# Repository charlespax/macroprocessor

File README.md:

# macroprocessor
A project to create a microprocessor optimized for human visual verification

# Introduction
A user should be able to trust the output of a computational device without having to trust
the computatoinal device itself.

# Application
## Cryptographic security
Bitcoin

# Design
The design is not optimized for price, area, power, efficiency, yield, or other 
traditional parameter. The design is optimized for human readability and understanding.

## Requirements
- MUST be visible to a human with minimal optical magnification
- An integrated circuit design layout SHOULD aid understanding
- IC layout SHOULD correspond to the layout as seen in a digitial simulation
- Microprocessor design architecture SHOULD be optimized for understanding
- The registers or other circuitry MAY emit light
- MAY have features to aid cryptography
- MAY have serial output for debugging or other purposes

## Design notes
The overall chip layout and data flow SHOULD run from left to right.

Logical elements SHOULD have inputs on the left and outputs on the right

The metal layer or other features MUST NOT obscure any features such that 
the circuit can not be verified visually.

Chip packaging MUST NOT obscure the electrical path from the IC to the
package pins.

The design MAY use multiple IC components if each component meets the
requirements of this document.

The design MAY include wire-bonded components

# Notes
- RISC-V RV32I or RV32E are candidates
- Research making a Forth-native processor
- Can the macroprocessor be made using the same process as LEDs?
- Can a wafer be put through a secondary LED process to create registers that
  emit light?
- What is the current state of light-emitting transistors (LETs)?
- Can I use diode logic and use LEDs?
- I believe the normal silicon process cannot be used to create features that
  emit light because the band gap of silicon is too greaet. True?
- RISC-V would be a great choice if it can be visually verified. This has the 
  advantage that many more eyes would be on the chip. However, I think it is
  more important to make choices that result in more users in verifying their
  own devices.
- Check out https://zeroToASICCourse.com - this is a course for designing and ordering
  your own chip designs.
- Check out https://developers.google.com/silicon - Google's wafer batching
  program for open source designs. Cool, but I am happy to pay if reasonable.
- MAY take an external diode-based ROM
- Is there anything about this processor that would make it bad at cryptographic
  functions? Minimal circuitry could be included to address issues.
- Can x-ray crystalography be used to verify the surface of an IC?
- https://www.skywatertechnology.com is a US-based silicon fab. 
- What happens to the equipment from old semiconductor fabrication technologies?
- Fab technologies: https://en.wikipedia.org/wiki/Semiconductor\_device\_fabrication
- Are there fabs that use old technologies for new chips?
- Wire bonding can be used in places where the metal layer would obscure layers below
- wire bonding can be used as jumpers that can be cut to permanently disable a ffeature
- Rather than wire bonding, the connections can be routed to the outside of the package,
  so they can be explicetly enabled
- Maybe multi gate transistors can be used on such large features if one large gate is
  not appropriate
- Make the binary instruction decoding physicallyl easy to see on the die. Put them
  in the same order you would find them in a specification table
- Is silicon transparent to any frequency of light? If so, maybe  this can be
  used for verification and would be a design consideration.

# Conventions
The keywords below are to be interpreted as described in BCP14 [RFC2119] [RFC8174].
- MUST
- MUST NOT
- REQUIRED
- SHOULD
- SHOULD NOT
- RECOMMENDED
- NOT RECOMMENDED
- MAY
- OPTIONAL

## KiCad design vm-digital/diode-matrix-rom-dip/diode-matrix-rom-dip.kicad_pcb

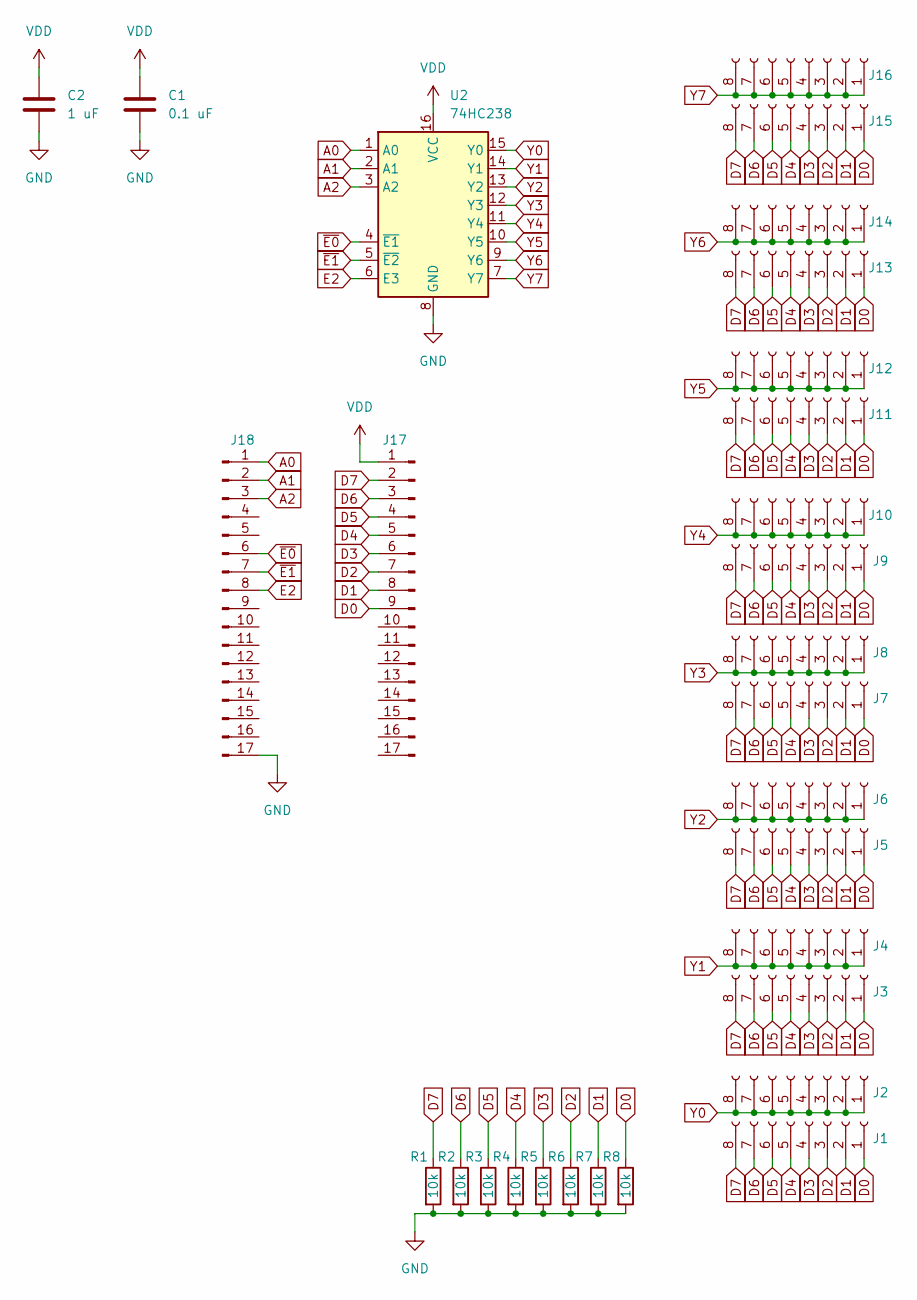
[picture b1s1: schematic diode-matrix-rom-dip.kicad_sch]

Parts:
C1: 0.1 uF; C_1206_3216Metric_Pad1.33x1.80mm_HandSolder
C2: 1 uF; C_1206_3216Metric_Pad1.33x1.80mm_HandSolder
J1, J2, J3, J4, J5, J6, J7, J8, J9, J10, J11, J12, J13, J14, J15, J16: Conn_01x08_Socket; PinSocket_1x08_P2.54mm_Vertical
J17, J18: Conn_01x17_Pin; PinHeader_1x17_P2.54mm_Vertical
R1, R2, R3, R4, R5, R6, R7, R8: 10k; R_0201_0603Metric
U2: 74HC238; DIP-16_W7.62mm

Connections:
A0: J18.1, U2.1 (A0)
A1: J18.2, U2.2 (A1)
A2: J18.3, U2.3 (A2)
D0: J1.1, J3.1, J5.1, J7.1, J9.1, J11.1, J13.1, J15.1, J17.9, R8.1
D1: J1.2, J3.2, J5.2, J7.2, J9.2, J11.2, J13.2, J15.2, J17.8, R7.1
D2: J1.3, J3.3, J5.3, J7.3, J9.3, J11.3, J13.3, J15.3, J17.7, R6.1
D3: J1.4, J3.4, J5.4, J7.4, J9.4, J11.4, J13.4, J15.4, J17.6, R5.1
D4: J1.5, J3.5, J5.5, J7.5, J9.5, J11.5, J13.5, J15.5, J17.5, R4.1
D5: J1.6, J3.6, J5.6, J7.6, J9.6, J11.6, J13.6, J15.6, J17.4, R3.1
D6: J1.7, J3.7, J5.7, J7.7, J9.7, J11.7, J13.7, J15.7, J17.3, R2.1
D7: J1.8, J3.8, J5.8, J7.8, J9.8, J11.8, J13.8, J15.8, J17.2, R1.1
E2: J18.8, U2.6 (E3)
GND: C1.2, C2.2, J18.17, R1.2, R2.2, R3.2, R4.2, R5.2, R6.2, R7.2, R8.2, U2.8 (GND)
VDD: C1.1, C2.1, J17.1, U2.16 (VCC)
Y0: J2.1, J2.2, J2.3, J2.4, J2.5, J2.6, J2.7, J2.8, U2.15 (Y0)
Y1: J4.1, J4.2, J4.3, J4.4, J4.5, J4.6, J4.7, J4.8, U2.14 (Y1)
Y2: J6.1, J6.2, J6.3, J6.4, J6.5, J6.6, J6.7, J6.8, U2.13 (Y2)
Y3: J8.1, J8.2, J8.3, J8.4, J8.5, J8.6, J8.7, J8.8, U2.12 (Y3)
Y4: J10.1, J10.2, J10.3, J10.4, J10.5, J10.6, J10.7, J10.8, U2.11 (Y4)
Y5: J12.1, J12.2, J12.3, J12.4, J12.5, J12.6, J12.7, J12.8, U2.10 (Y5)
Y6: J14.1, J14.2, J14.3, J14.4, J14.5, J14.6, J14.7, J14.8, U2.9 (Y6)
Y7: J16.1, J16.2, J16.3, J16.4, J16.5, J16.6, J16.7, J16.8, U2.7 (Y7)
~E0: J18.6, U2.4 (~E1)
~E1: J18.7, U2.5 (~E2)

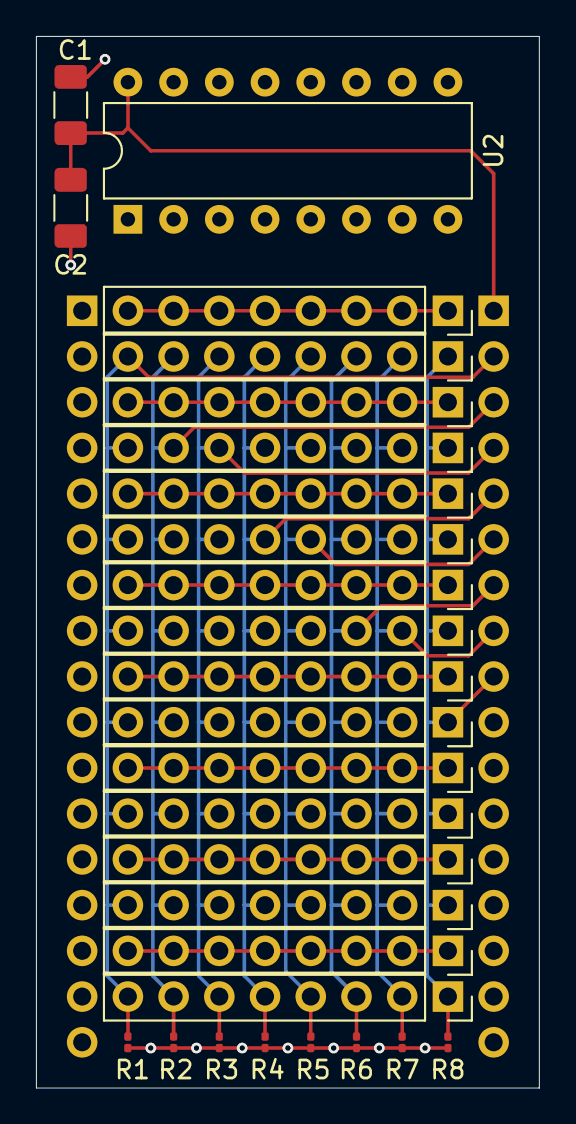
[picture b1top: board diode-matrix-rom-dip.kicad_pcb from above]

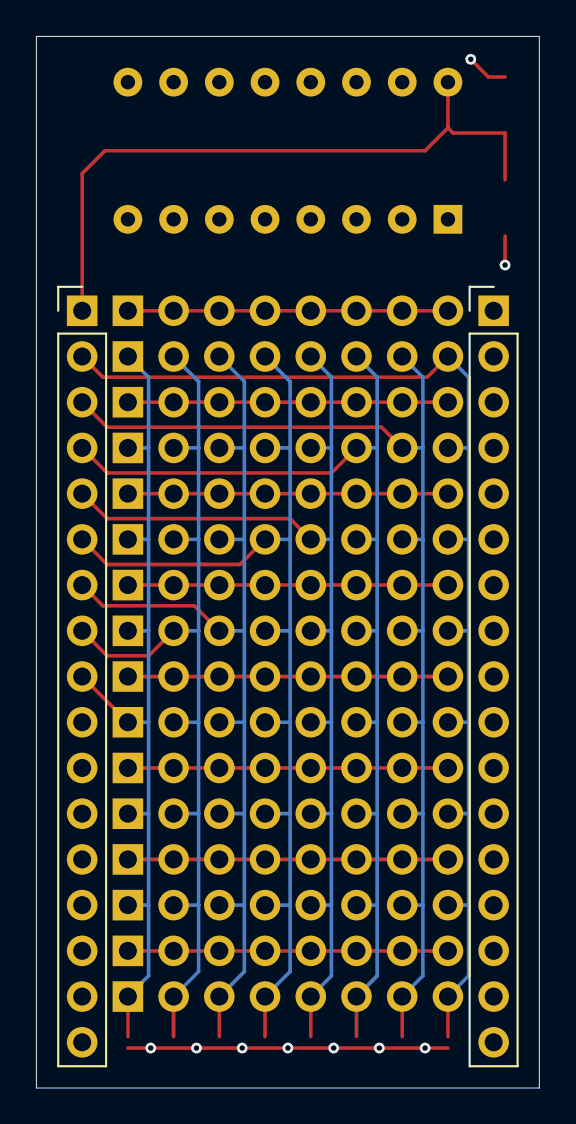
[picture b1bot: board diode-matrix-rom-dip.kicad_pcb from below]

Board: 4 copper layers, 27.9 x 58.4 mm, 29 parts (2 on the bottom side), 24 nets.

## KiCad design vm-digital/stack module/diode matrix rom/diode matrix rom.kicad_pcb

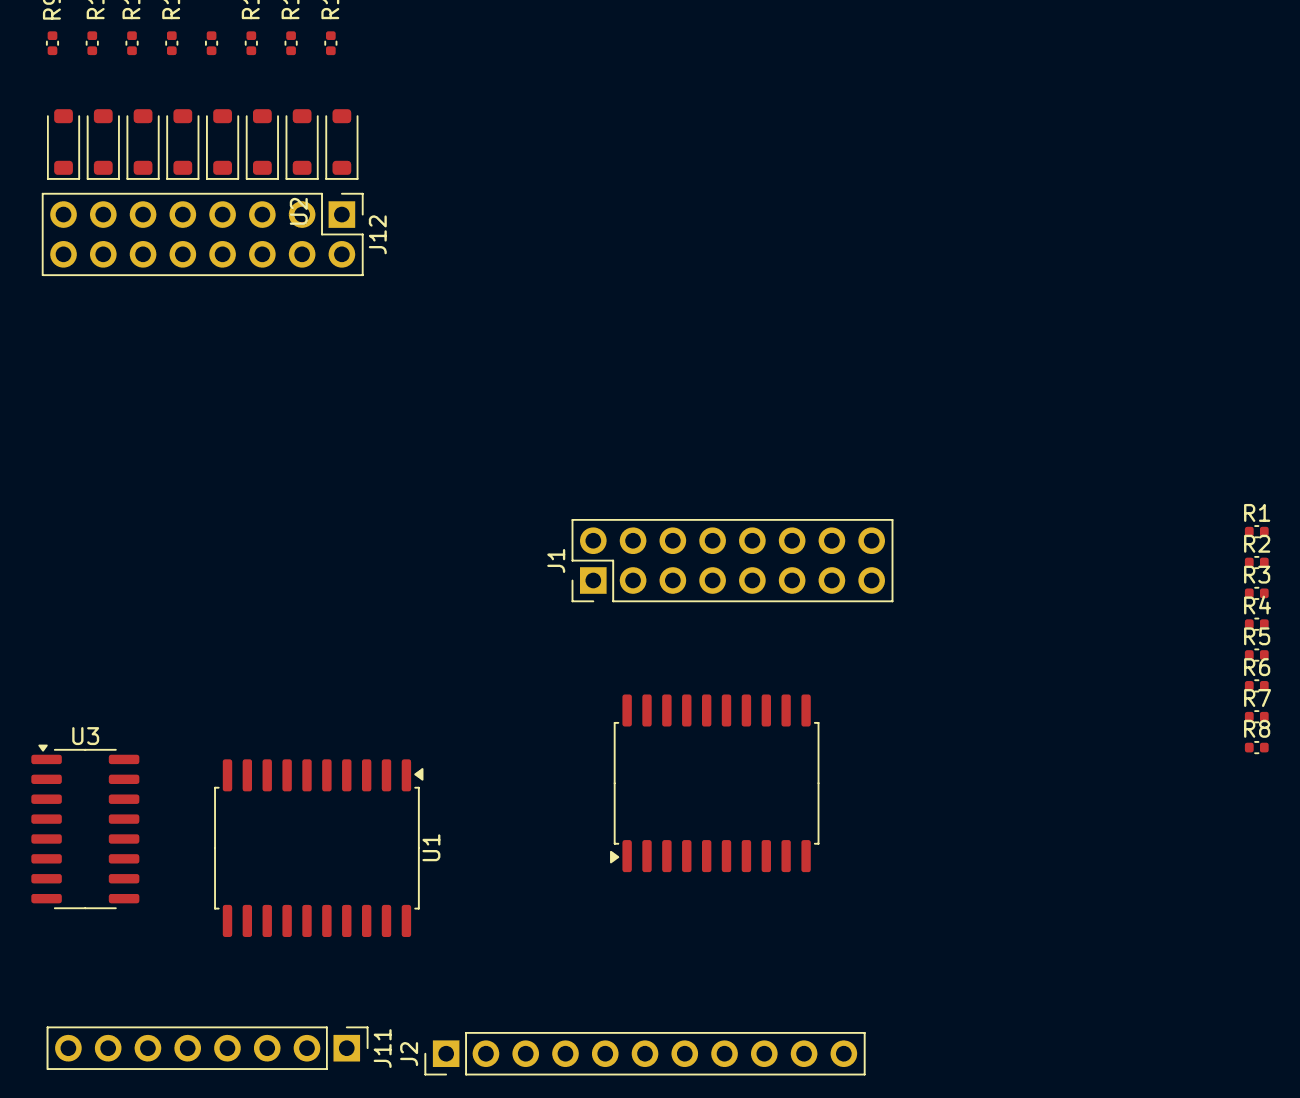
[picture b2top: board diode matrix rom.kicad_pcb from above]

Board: 2 copper layers, 31 parts (0 on the bottom side), 47 nets, no tracks yet.

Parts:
D1, D2, D3, D4, D5, D6, D7, D8: D; D_SOD-123
J1, J12: DIN41612_02x16_AB; PinHeader_2x08_P2.54mm_Vertical
J2: Conn_01x11_Pin; PinHeader_1x11_P2.54mm_Vertical
J11: Conn_01x08_Pin; PinHeader_1x08_P2.54mm_Vertical
R1, R2, R3, R4, R5, R6, R7, R8, R9, R10, R11, R12, R13, R14, R15, R16: 10k; C_0402_1005Metric
U1: 74LS540; SOIC-20W_7.5x12.8mm_P1.27mm
U2: 74HC688; SOIC-20W_7.5x12.8mm_P1.27mm
U3: 74HC238; SOIC-16_3.9x9.9mm_P1.27mm

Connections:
B0: D1.2 (A), R16.2, U1.2 (A0)
B1: D2.2 (A), R15.2, U1.3 (A1)
B2: D4.2 (A), R14.2, U1.4 (A2)
B3: D3.2 (A), R13.2, U1.5 (A3)
B4: D8.2 (A), R12.2, U1.6 (A4)
B5: D7.2 (A), R11.2, U1.7 (A5)
B6: D6.2 (A), R10.2, U1.8 (A6)
B7: D5.2 (A), R9.2, U1.9 (A7)
GND: R1.1, R2.1, R3.1, R4.1, R5.1, R6.1, R7.1, R8.1, U1.10 (GND), U2.10 (GND), U3.8 (GND)
unnamed: D1.1 (K), J12.1
unnamed: D2.1 (K), J12.3
unnamed: D3.1 (K), J12.7
unnamed: D4.1 (K), J12.5
unnamed: D5.1 (K), J12.15
unnamed: D6.1 (K), J12.13
unnamed: D7.1 (K), J12.11
unnamed: D8.1 (K), J12.9
unnamed: J1.2, R1.2, U2.2 (P0)
unnamed: J1.4, R2.2, U2.4 (P1)
unnamed: J1.6, R3.2, U2.6 (P2)
unnamed: J1.8, R4.2, U2.8 (P3)
unnamed: J1.10, R5.2, U2.11 (P4)
unnamed: J1.12, R6.2, U2.13 (P5)
unnamed: J1.14, R7.2, U2.15 (P6)
unnamed: J1.16, R8.2, U2.17 (P7)
unnamed: J2.1, U3.1 (A0)
unnamed: J2.2, U3.2 (A1)
unnamed: J2.3, U3.3 (A2)
unnamed: J2.4, U2.3 (R0)
unnamed: J2.5, U2.5 (R1)
unnamed: J2.6, U2.7 (R2)
unnamed: J2.7, U2.9 (R3)
unnamed: J2.8, U2.12 (R4)
unnamed: J2.9, U2.14 (R5)
unnamed: J2.10, U2.16 (R6)
unnamed: J2.11, U2.18 (R7)
unnamed: J11.1, U1.18 (Y0)
unnamed: J11.2, U1.17 (Y1)
unnamed: J11.3, U1.16 (Y2)
unnamed: J11.4, U1.15 (Y3)
unnamed: J11.5, U1.14 (Y4)
unnamed: J11.6, U1.13 (Y5)
unnamed: J11.7, U1.12 (Y6)
unnamed: J11.8, U1.11 (Y7)
unnamed: U1.1 (G1), U1.19 (G2), U2.19 (P=R), U3.4 (~E0), U3.5 (~E1)
VDD: J1.1, J1.3, J1.5, J1.7, J1.9, J1.11, J1.13, J1.15, R9.1, R10.1, R11.1, R12.1, R13.1, R14.1, R15.1, R16.1, U1.20 (VCC), U2.20 (VCC), U3.6 (E2), U3.16 (VCC)
W0: J12.2, J12.4, J12.6, J12.8, J12.10, J12.12, J12.14, J12.16, U3.15 (~Y0)

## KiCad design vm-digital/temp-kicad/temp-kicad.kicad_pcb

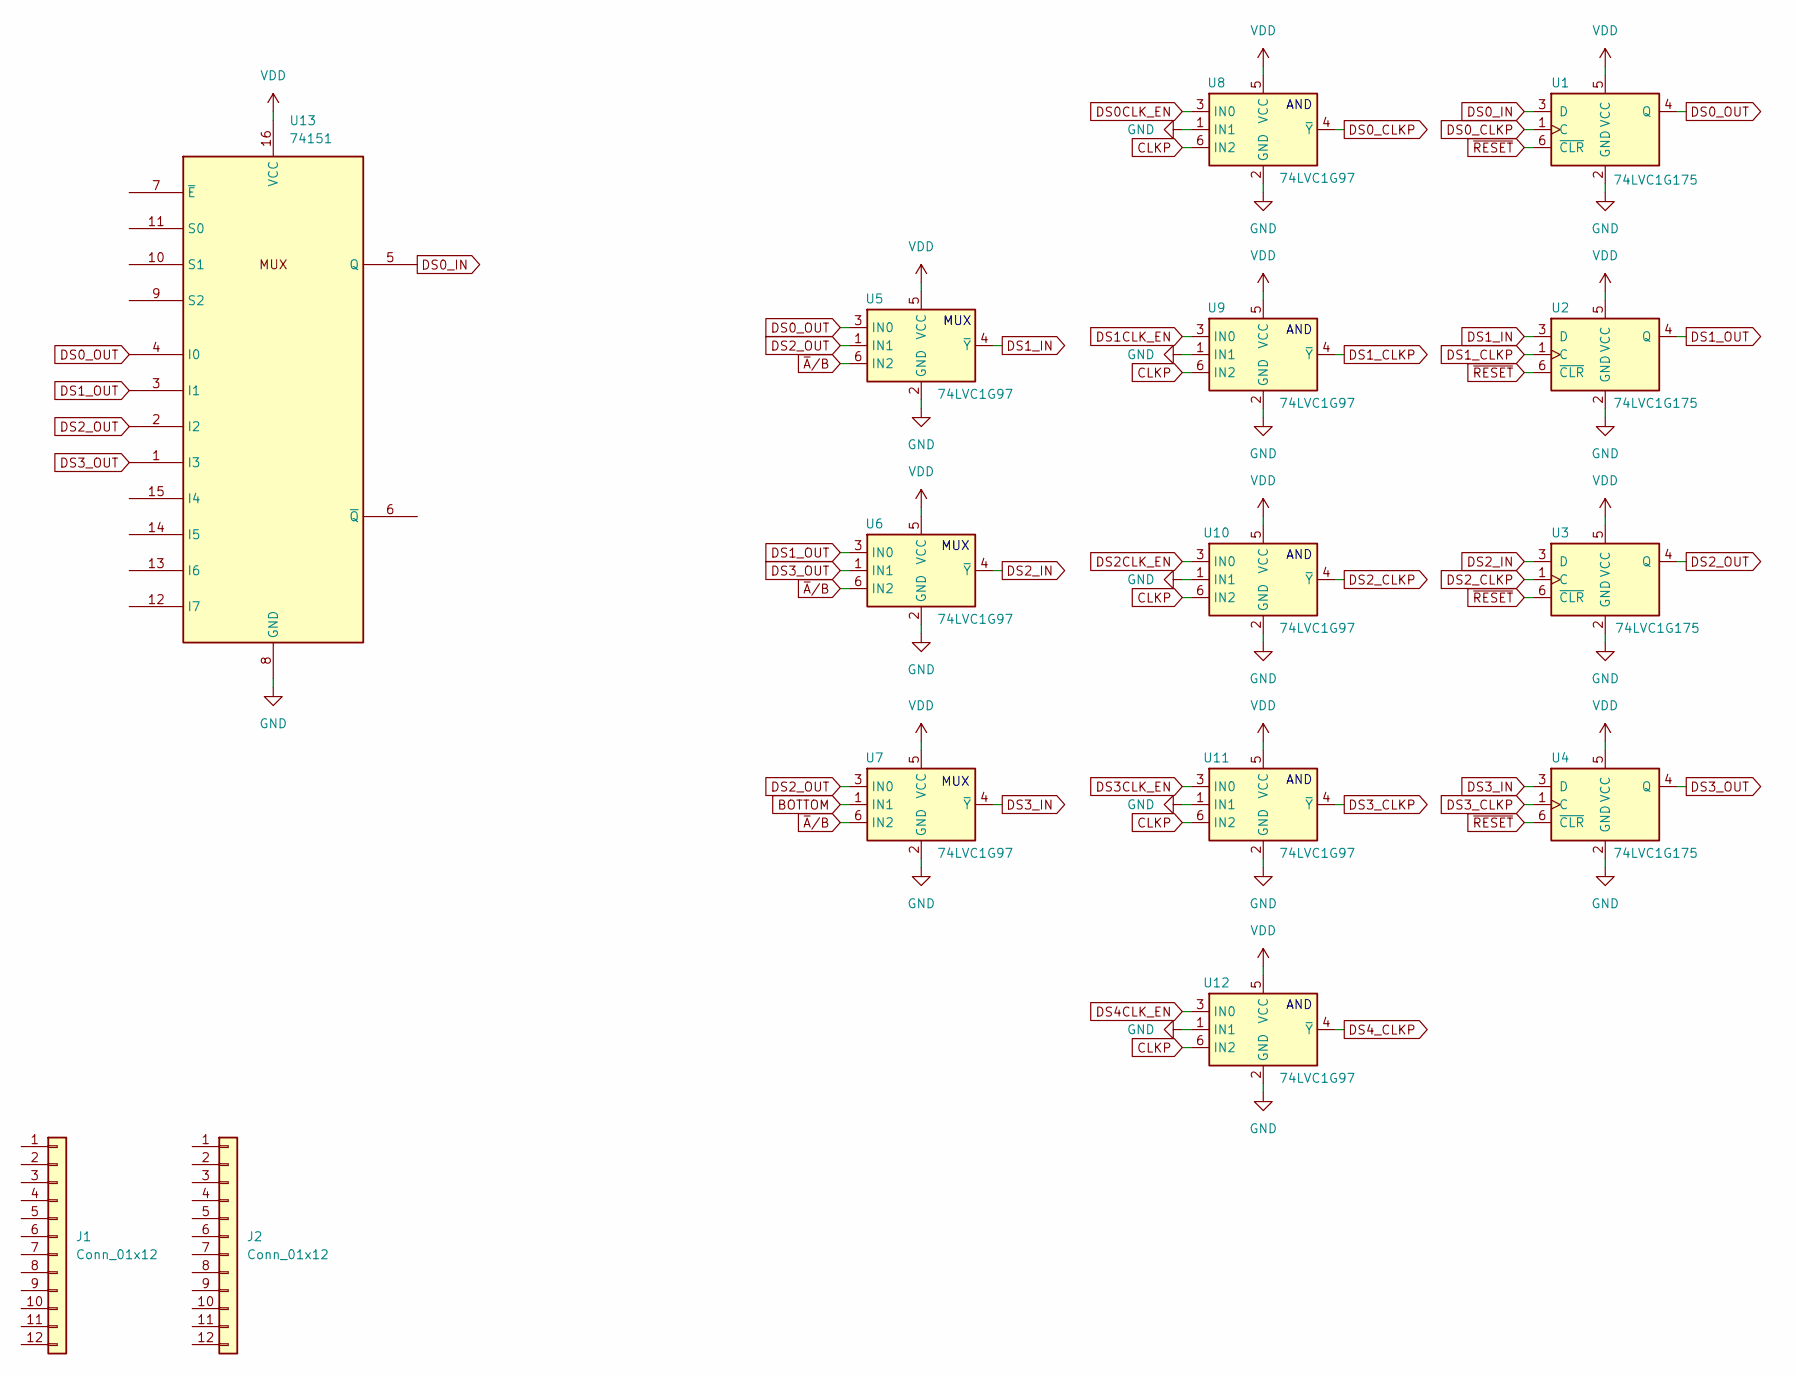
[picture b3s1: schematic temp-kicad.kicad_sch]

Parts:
J1, J2: Conn_01x12; PinHeader_1x12_P2.54mm_Vertical
U1, U2, U3, U4: 74LVC1G175; SOT-23-6_Handsoldering
U5, U6, U7, U8, U9, U10, U11, U12: 74LVC1G97; SOT-23-6_Handsoldering
U13: 74151; SOIC-16_3.9x9.9mm_P1.27mm

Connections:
BOTTOM: U7.1 (IN1)
CLKP: U8.6 (IN2), U9.6 (IN2), U10.6 (IN2), U11.6 (IN2), U12.6 (IN2)
DS0CLK_EN: U8.3 (IN0)
DS0_CLKP: U1.1 (C), U8.4 (~Y)
DS0_IN: U1.3 (D), U13.5 (Q)
DS0_OUT: U1.4 (Q), U5.3 (IN0), U13.4 (I0)
DS1CLK_EN: U9.3 (IN0)
DS1_CLKP: U2.1 (C), U9.4 (~Y)
DS1_IN: U2.3 (D), U5.4 (~Y)
DS1_OUT: U2.4 (Q), U6.3 (IN0), U13.3 (I1)
DS2CLK_EN: U10.3 (IN0)
DS2_CLKP: U3.1 (C), U10.4 (~Y)
DS2_IN: U3.3 (D), U6.4 (~Y)
DS2_OUT: U3.4 (Q), U5.1 (IN1), U7.3 (IN0), U13.2 (I2)
DS3CLK_EN: U11.3 (IN0)
DS3_CLKP: U4.1 (C), U11.4 (~Y)
DS3_IN: U4.3 (D), U7.4 (~Y)
DS3_OUT: U4.4 (Q), U6.1 (IN1), U13.1 (I3)
DS4CLK_EN: U12.3 (IN0)
DS4_CLKP: U12.4 (~Y)
GND: U1.2 (GND), U2.2 (GND), U3.2 (GND), U4.2 (GND), U5.2 (GND), U6.2 (GND), U7.2 (GND), U8.1 (IN1), U8.2 (GND), U9.1 (IN1), U9.2 (GND), U10.1 (IN1), U10.2 (GND), U11.1 (IN1), U11.2 (GND), U12.1 (IN1), U12.2 (GND), U13.8 (GND)
VDD: U1.5 (VCC), U2.5 (VCC), U3.5 (VCC), U4.5 (VCC), U5.5 (VCC), U6.5 (VCC), U7.5 (VCC), U8.5 (VCC), U9.5 (VCC), U10.5 (VCC), U11.5 (VCC), U12.5 (VCC), U13.16 (VCC)
~A/B: U5.6 (IN2), U6.6 (IN2), U7.6 (IN2)
~RESET: U1.6 (~CLR), U2.6 (~CLR), U3.6 (~CLR), U4.6 (~CLR)

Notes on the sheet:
MUX
AND

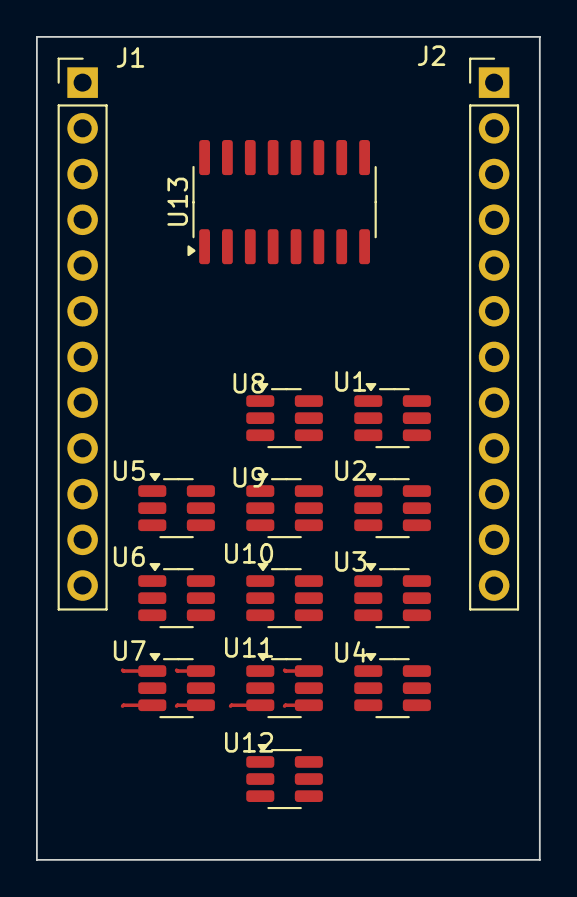
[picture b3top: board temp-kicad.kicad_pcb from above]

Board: 4 copper layers, 27.9 x 45.7 mm, 15 parts (0 on the bottom side), 17 nets.

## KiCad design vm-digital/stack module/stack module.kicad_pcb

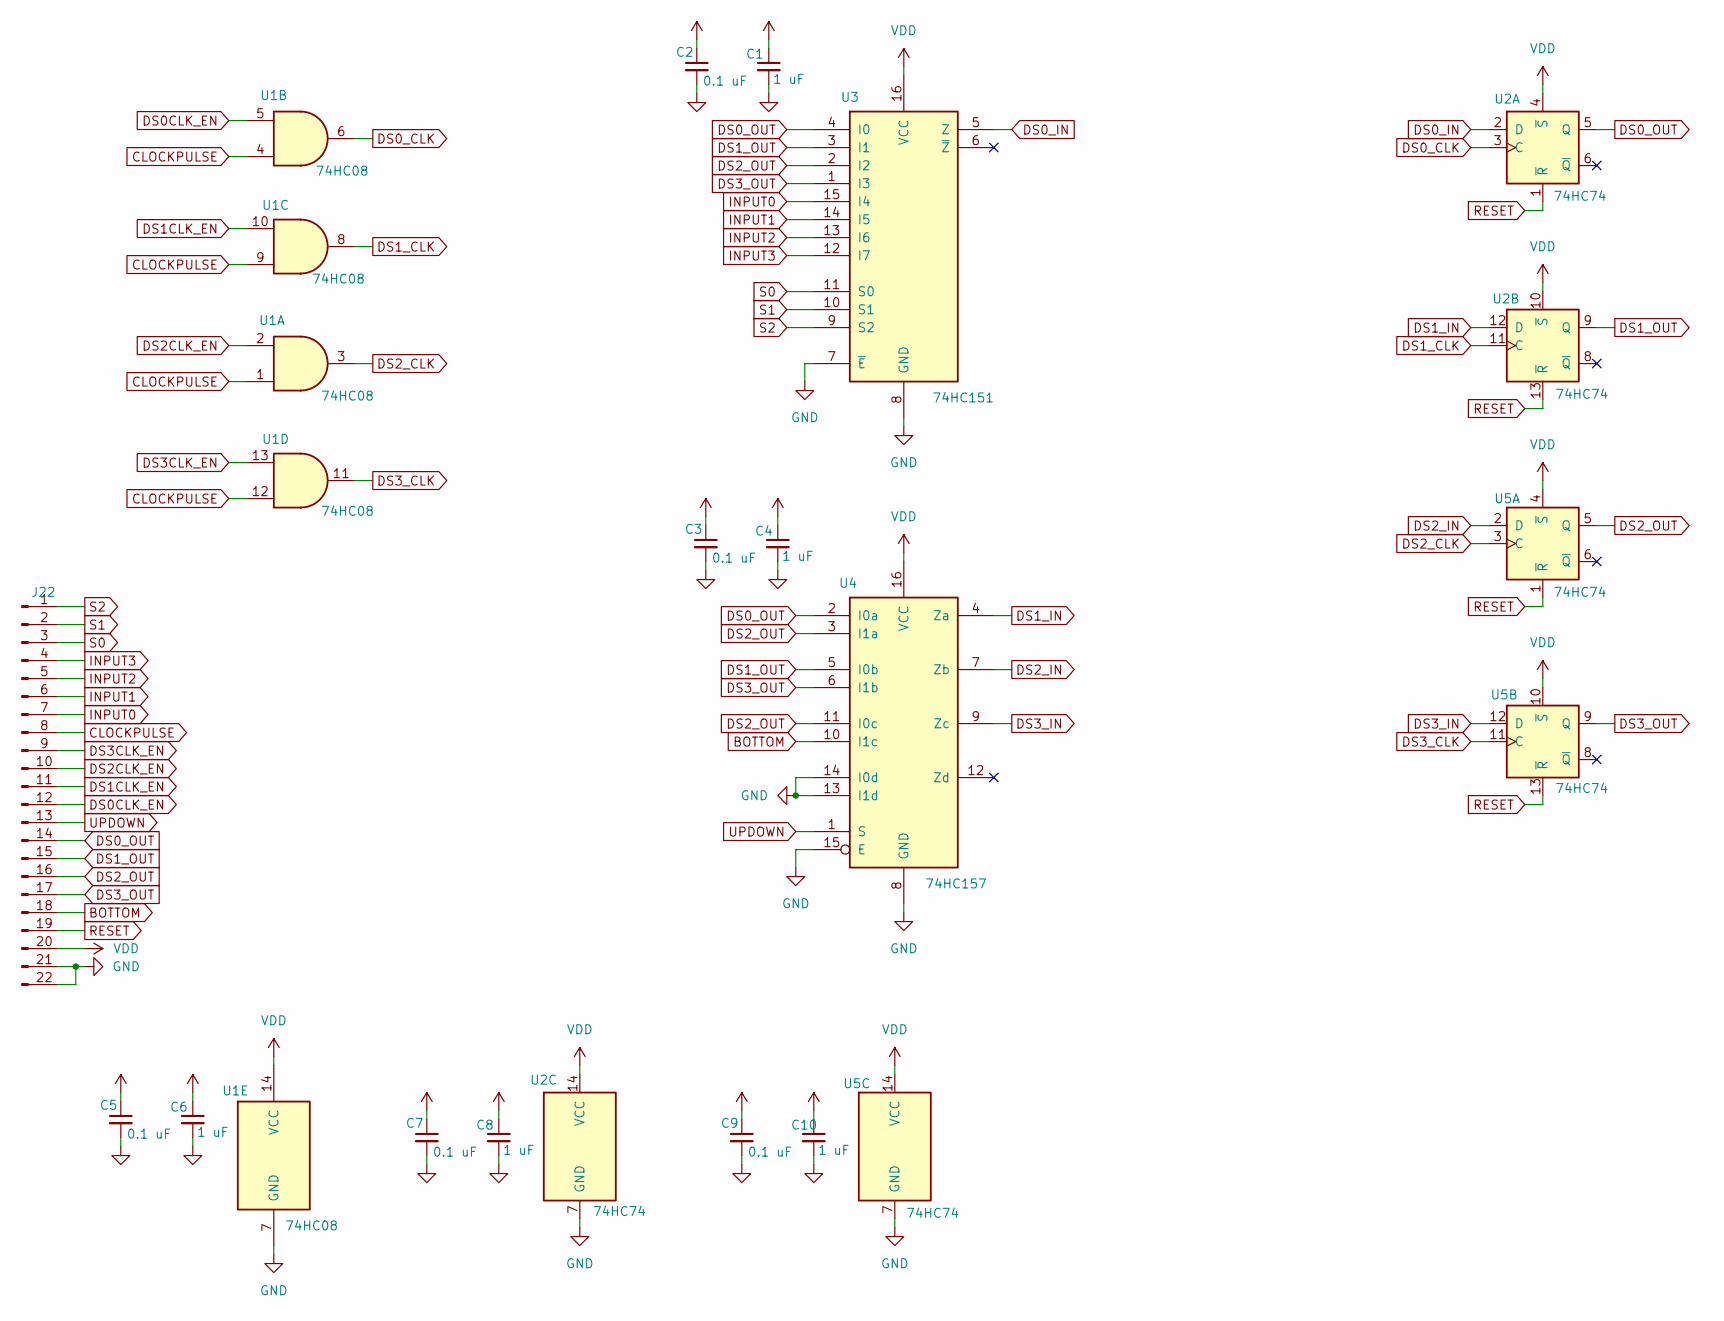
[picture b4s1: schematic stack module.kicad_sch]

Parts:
C1, C4, C6, C8, C10: 1 uF; C_1206_3216Metric_Pad1.33x1.80mm_HandSolder
C2, C3, C5, C7, C9: 0.1 uF; C_1206_3216Metric_Pad1.33x1.80mm_HandSolder
J22: Conn_01x22_Pin; PinHeader_1x22_P2.54mm_Vertical
U1: 74HC08; DIP-14_W7.62mm_Socket_LongPads
U2, U5: 74HC74; DIP-14_W7.62mm_Socket_LongPads
U3: 74HC151; DIP-16_W7.62mm_Socket_LongPads
U4: 74HC157; DIP-16_W7.62mm_Socket_LongPads

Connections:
BOTTOM: J22.18, U4.10 (I1c)
CLOCKPULSE: J22.8, U1.1, U1.4, U1.9, U1.12
DS0CLK_EN: J22.12, U1.5
DS0_CLK: U1.6, U2.3 (C)
DS0_IN: U2.2 (D), U3.5 (Z)
DS0_OUT: J22.14, U2.5 (Q), U3.4 (I0), U4.2 (I0a)
DS1CLK_EN: J22.11, U1.10
DS1_CLK: U1.8, U2.11 (C)
DS1_IN: U2.12 (D), U4.4 (Za)
DS1_OUT: J22.15, U2.9 (Q), U3.3 (I1), U4.5 (I0b)
DS2CLK_EN: J22.10, U1.2
DS2_CLK: U1.3, U5.3 (C)
DS2_IN: U4.7 (Zb), U5.2 (D)
DS2_OUT: J22.16, U3.2 (I2), U4.3 (I1a), U4.11 (I0c), U5.5 (Q)
DS3CLK_EN: J22.9, U1.13
DS3_CLK: U1.11, U5.11 (C)
DS3_IN: U4.9 (Zc), U5.12 (D)
DS3_OUT: J22.17, U3.1 (I3), U4.6 (I1b), U5.9 (Q)
GND: C1.2, C2.2, C3.2, C4.2, C5.2, C6.2, C7.2, C8.2, C9.2, C10.2, J22.21, J22.22, U1.7 (GND), U2.7 (GND), U3.7 (~E), U3.8 (GND), U4.8 (GND), U4.13 (I1d), U4.14 (I0d), U4.15 (E), U5.7 (GND)
INPUT0: J22.7, U3.15 (I4)
INPUT1: J22.6, U3.14 (I5)
INPUT2: J22.5, U3.13 (I6)
INPUT3: J22.4, U3.12 (I7)
RESET: J22.19, U2.1 (~R), U2.13 (~R), U5.1 (~R), U5.13 (~R)
S0: J22.3, U3.11 (S0)
S1: J22.2, U3.10 (S1)
S2: J22.1, U3.9 (S2)
UPDOWN: J22.13, U4.1 (S)
VDD: C1.1, C2.1, C3.1, C4.1, C5.1, C6.1, C7.1, C8.1, C9.1, C10.1, J22.20, U1.14 (VCC), U2.4 (~S), U2.10 (~S), U2.14 (VCC), U3.16 (VCC), U4.16 (VCC), U5.4 (~S), U5.10 (~S), U5.14 (VCC)

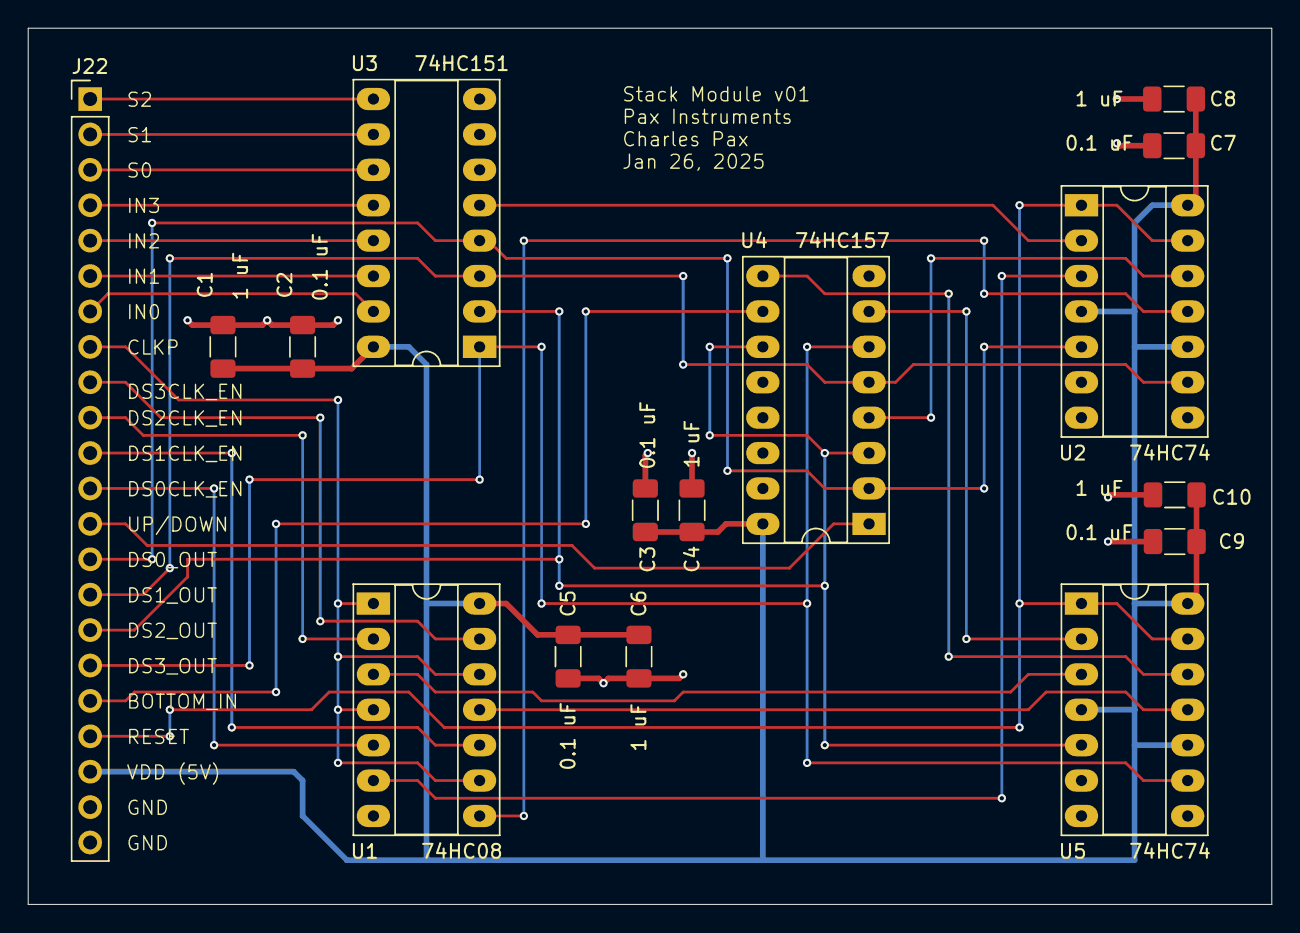
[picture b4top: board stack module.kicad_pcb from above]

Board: 2 copper layers, 89.2 x 62.9 mm, 16 parts (0 on the bottom side), 29 nets.

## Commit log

2022-12-20 Initial transcription of some of my paper notes.
2022-12-21 Added more notes.
2023-01-16 Adding older repo stuff.
2023-01-31 Added notes for stack machine instructions.
2023-01-31 Added a stack machine diagram.
2023-02-02 Added a block diagram. Added ISA.
2023-02-03 Added doc.txt for documentation in Forth format.
2023-02-03 Updated doc.txt.
2023-02-03 Removed old isa.txt.
2023-02-03 Added infor to the doc.txt file.
2023-02-04 Added scratchpad.txt.
2023-02-04 Added more notes into doc.txt.
2023-02-05 added notes to doc.txt.
2023-02-05 Added my notes from the weekend.
2023-02-06 Moved notes into doc.txt.
2023-02-06 Added print.sh, which prints the text fifty lines at a time to the default printer.
2023-02-06 Added notes. Reformatted to 64 lines per page.
2023-02-08 Added instruction cycle information.
2023-02-08 Just some quick notes.
2023-02-09 Added notes.
2023-02-10 Added larger diagram. updated print script. Added 3d cube to scratchpad.
2023-02-10 Using DS++ rather than DS+. Formatting.
2023-02-10 Final format and print for the day. No notes for now.
2023-02-13 v2023-02-09
2023-02-14 Small change.
2023-02-15 Added new edits for today.
2023-02-16 Started adding notes from lastnight.
2023-02-17 Added notes for the day.
2023-02-17 Finished enter notes from yesterday.
2023-03-03 Added some edits.
2023-12-12 Added the book templates.
2023-12-12 Added dot files.
2023-12-12 Added notes on forth. Add these to book and remove.
2023-12-12 Added a director for vm-digital
2023-12-12 added apt-get command for installing the required packages for compilation on Linux Mint 21.2.
2023-12-13 added Forth dictionary entry format information. Removed pdf.
2023-12-15 Added a diagram for the word format. This is to help think about how the address interpreter works.
2023-12-20 added a architrcture block diagram.
2023-12-20 - improved figures, moved text - improved address format figure
2023-12-20 Typeset ISA table.
2023-12-20 Added the old text file.
2023-12-20 Retired the original doc.txt.
2023-12-21 adding some text.
2023-12-21 Added headers to the dictionary entry format figure.
2023-12-22 got the glossary working
2023-12-23 Added a bunch of books to the bib.
2023-12-24 Added a table showing the stepwise execution of a Forth word.
2023-12-25 Added the ascii timing chart.
2023-12-28 Added code listings for some words.
2024-11-26 added some notes
2024-11-26 updated required package installation list
2024-11-27 added spaces to glossary for better vim navigation
2024-11-27 transferred notes from paper
2024-12-25 added isa.txt
2024-12-25 added a HDigital circuit for a bit lice ALU
2024-12-27 updated isa
2024-12-29 Added forth words and truth tables. moved essential functions to the first multiplexer.
2024-12-29 forth.txt
2024-12-29 sorted the mux inputs according to the isa
2025-01-02 added a diode matrix rom to the simulation
2025-01-03 rom is better. has isa implemented. binary counter cycles through rom.
2025-01-04 simulation steps through diode matrix rom
2025-01-06 forth.txt single line docs
2025-01-27 added a stack module PCB design and some hmdigital circuits.
2025-01-29 added a small stack module experiment.
2025-02-04 added some kicad files.
2025-02-14 nothing
2025-02-14 Added diode-matrix-rom-dip
2025-02-14 stack-dip
2025-02-18 main board
2025-12-01 cleaning up
